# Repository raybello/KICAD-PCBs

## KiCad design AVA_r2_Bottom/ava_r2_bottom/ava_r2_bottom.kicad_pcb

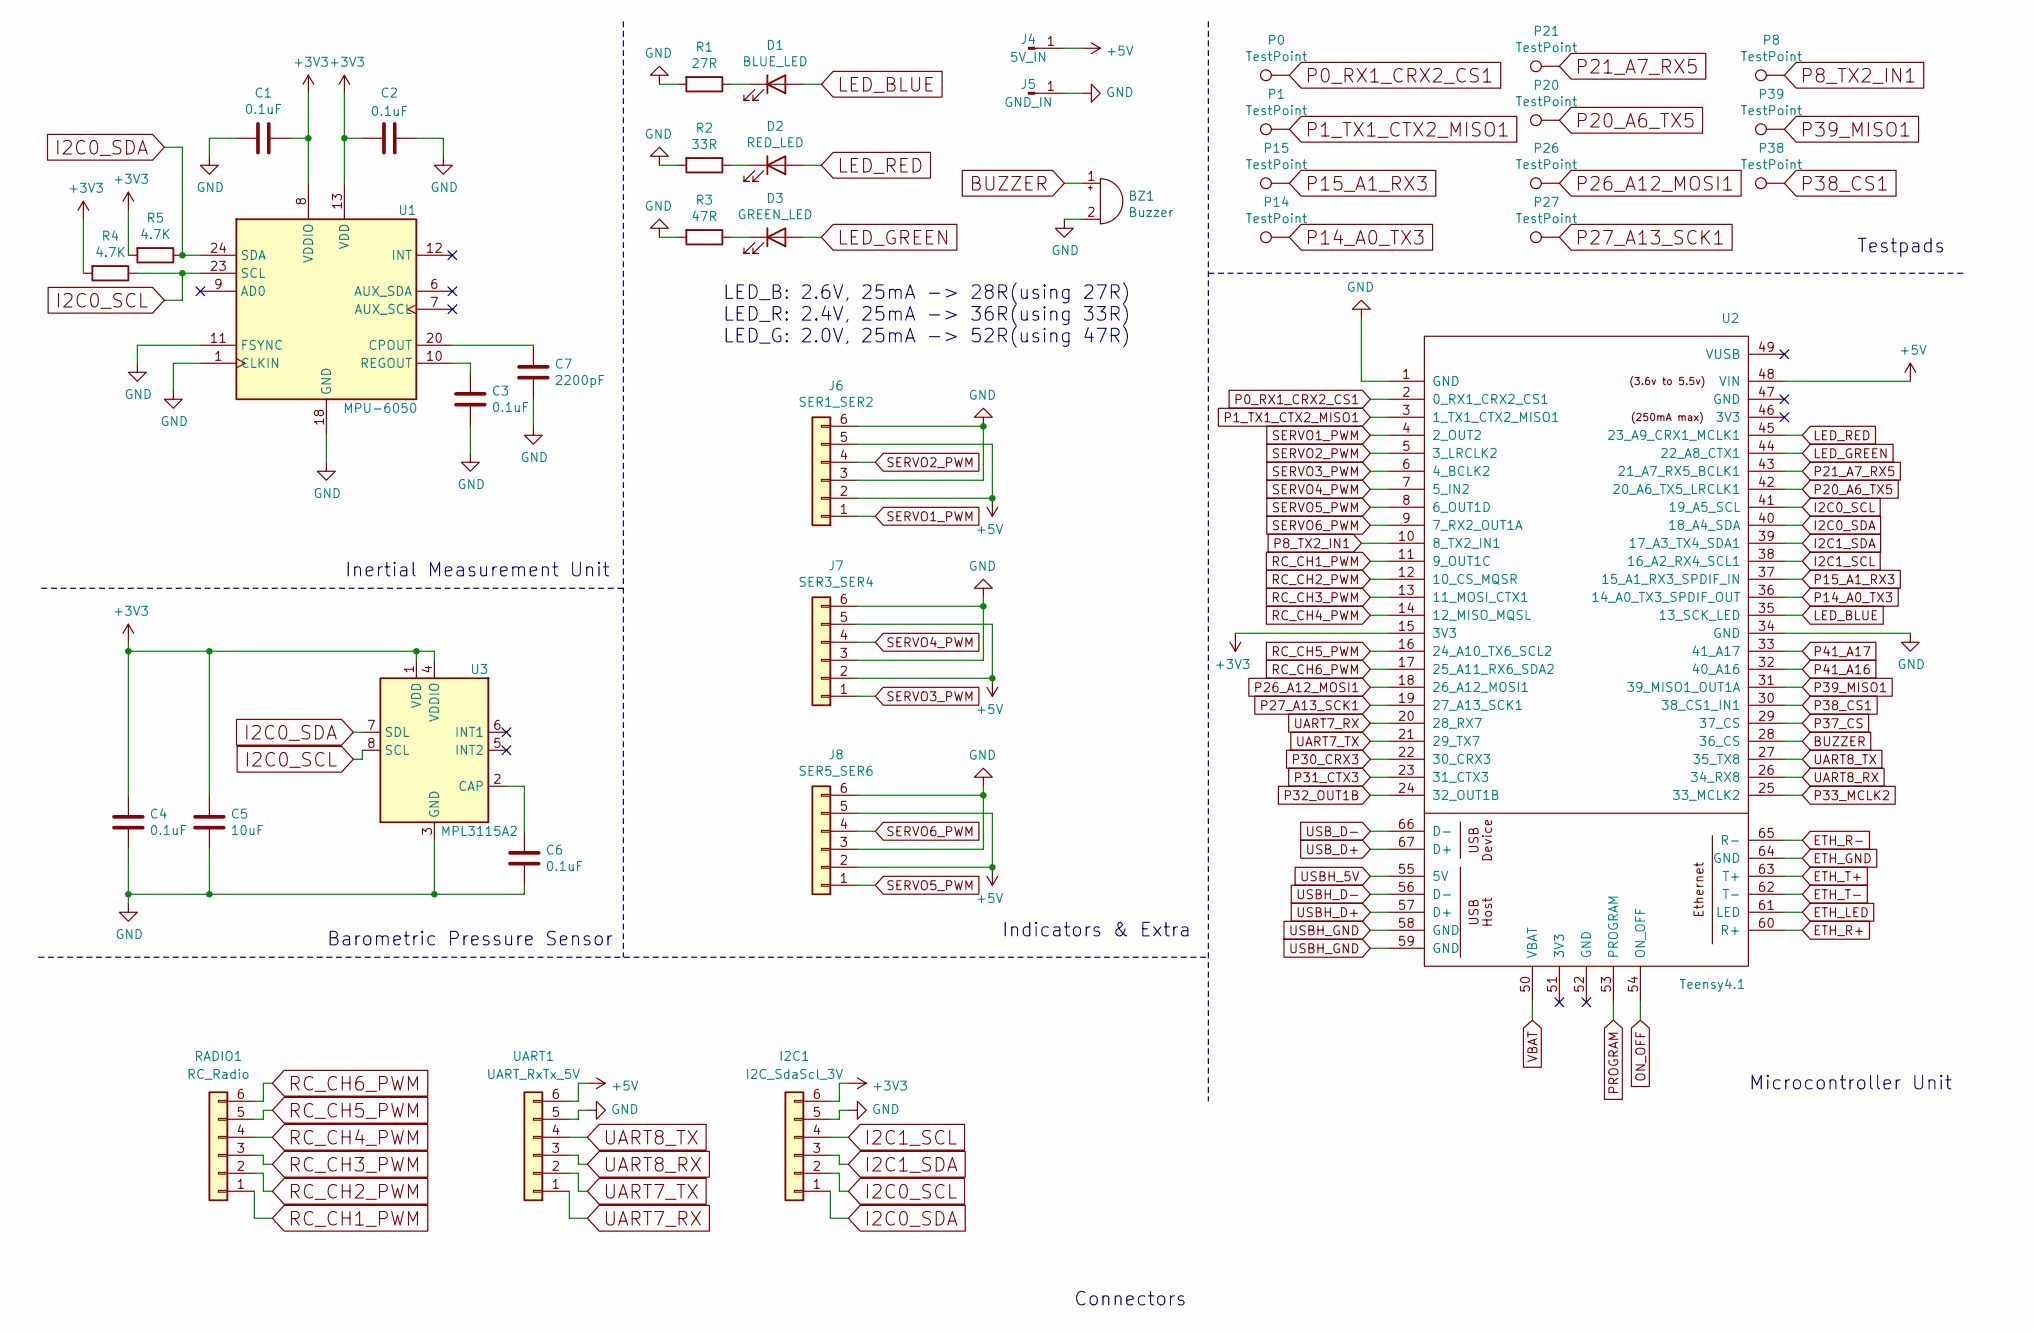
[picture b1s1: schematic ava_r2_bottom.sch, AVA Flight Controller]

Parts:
BZ1: Buzzer; Buzzer_TDK_PS1240P02BT_D12.2mm_H6.5mm
C1, C2, C3, C4, C6: 0.1uF; C_0805_2012Metric_Pad1.18x1.45mm_HandSolder
C5: 10uF; C_0805_2012Metric_Pad1.18x1.45mm_HandSolder
C7: 2200pF; C_0805_2012Metric_Pad1.18x1.45mm_HandSolder
D1: BLUE_LED; LED_0805_2012Metric_Pad1.15x1.40mm_HandSolder
D2: RED_LED; LED_0805_2012Metric_Pad1.15x1.40mm_HandSolder
D3: GREEN_LED; LED_0805_2012Metric_Pad1.15x1.40mm_HandSolder
I2C1: I2C_SdaScl_3V; JST_XH_B6B-XH-A_1x06_P2.50mm_Vertical
J4: 5V_IN; TestPoint_Pad_2.0x2.0mm
J5: GND_IN; TestPoint_Pad_D2.0mm
J6: SER1_SER2; PinHeader_1x06_P1.27mm_Vertical
J7: SER3_SER4; PinHeader_1x06_P1.27mm_Vertical
J8: SER5_SER6; PinHeader_1x06_P1.27mm_Vertical
P0, P1, P8, P14, P15, P20, P21, P26, P27, P38, P39: TestPoint; TestPoint_Pad_2.0x2.0mm
R1: 27R; R_Axial_DIN0207_L6.3mm_D2.5mm_P7.62mm_Horizontal
R2: 33R; R_Axial_DIN0207_L6.3mm_D2.5mm_P7.62mm_Horizontal
R3: 47R; R_Axial_DIN0207_L6.3mm_D2.5mm_P7.62mm_Horizontal
R4, R5: 4.7K; R_Axial_DIN0207_L6.3mm_D2.5mm_P7.62mm_Horizontal
RADIO1: RC_Radio; JST_XH_B6B-XH-A_1x06_P2.50mm_Vertical
U1: MPU-6050; InvenSense_QFN-24_4x4mm_P0.5mm
U2: Teensy4.1; Teensy41
U3: MPL3115A2; NXP_LGA-8_3x5mm_P1.25mm_H1.1mm
UART1: UART_RxTx_5V; JST_XH_B6B-XH-A_1x06_P2.50mm_Vertical

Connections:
+3V3: C1.1, C2.2, C4.2, C5.1, I2C1.6, R4.2, R5.2, U1.8 (VDDIO), U1.13 (VDD), U2.15 (3V3), U3.1 (VDD), U3.4 (VDDIO); also elsewhere on the board
+5V: J4.1, J6.2, J6.5, J7.2, J7.5, J8.2, J8.5, U2.48 (VIN), UART1.6
BUZZER: BZ1.1 (-), U2.28 (36_CS)
ETH_GND: U2.64 (GND)
ETH_LED: U2.61 (LED)
ETH_R+: U2.60 (R+)
ETH_R-: U2.65 (R-)
ETH_T+: U2.63 (T+)
ETH_T-: U2.62 (T-)
GND: BZ1.2 (+), C1.2, C2.1, C3.2, C4.1, C5.2, C6.1, C7.1, I2C1.5, J5.1, J6.3, J6.6, J7.3, J7.6, J8.3, J8.6, R1.2, R2.2, R3.2, U1.1 (CLKIN), U1.11 (FSYNC), U1.18 (GND), U2.1 (GND), U2.34 (GND), U3.3 (GND), UART1.5; also elsewhere on the board
I2C0_SCL: I2C1.2, R4.1, U1.23 (SCL), U2.41 (19_A5_SCL), U3.8 (SCL); also elsewhere on the board
I2C0_SDA: I2C1.1, R5.1, U1.24 (SDA), U2.40 (18_A4_SDA), U3.7 (SDL); also elsewhere on the board
I2C1_SCL: I2C1.4, U2.38 (16_A2_RX4_SCL1)
I2C1_SDA: I2C1.3, U2.39 (17_A3_TX4_SDA1)
LED_BLUE: D1.2 (A), U2.35 (13_SCK_LED)
LED_GREEN: D3.2 (A), U2.44 (22_A8_CTX1)
LED_RED: D2.2 (A), U2.45 (23_A9_CRX1_MCLK1)
unnamed 17: C3.1, U1.10 (REGOUT); also elsewhere on the board
unnamed: C6.2, U3.2 (CAP)
unnamed 19: C7.2, U1.20 (CPOUT); also elsewhere on the board
unnamed: D1.1 (K), R1.1
unnamed: D2.1 (K), R2.1
unnamed: D3.1 (K), R3.1
ON_OFF: U2.54 (ON_OFF)
P0_RX1_CRX2_CS1: P0.1, U2.2 (0_RX1_CRX2_CS1)
P1_TX1_CTX2_MISO1: P1.1, U2.3 (1_TX1_CTX2_MISO1)
P8_TX2_IN1: P8.1, U2.10 (8_TX2_IN1)
P14_A0_TX3: P14.1, U2.36 (14_A0_TX3_SPDIF_OUT)
P15_A1_RX3: P15.1, U2.37 (15_A1_RX3_SPDIF_IN)
P20_A6_TX5: P20.1, U2.42 (20_A6_TX5_LRCLK1)
P21_A7_RX5: P21.1, U2.43 (21_A7_RX5_BCLK1)
P26_A12_MOSI1: P26.1, U2.18 (26_A12_MOSI1)
P27_A13_SCK1: P27.1, U2.19 (27_A13_SCK1)
P30_CRX3: U2.22 (30_CRX3)
P31_CTX3: U2.23 (31_CTX3)
P32_OUT1B: U2.24 (32_OUT1B)
P33_MCLK2: U2.25 (33_MCLK2)
P37_CS: U2.29 (37_CS)
P38_CS1: P38.1, U2.30 (38_CS1_IN1)
P39_MISO1: P39.1, U2.31 (39_MISO1_OUT1A)
P41_A16: U2.32 (40_A16)
P41_A17: U2.33 (41_A17)
PROGRAM: U2.53 (PROGRAM)
RC_CH1_PWM: RADIO1.1, U2.11 (9_OUT1C)
RC_CH2_PWM: RADIO1.2, U2.12 (10_CS_MQSR)
RC_CH3_PWM: RADIO1.3, U2.13 (11_MOSI_CTX1)
RC_CH4_PWM: RADIO1.4, U2.14 (12_MISO_MQSL)
RC_CH5_PWM: RADIO1.5, U2.16 (24_A10_TX6_SCL2)
RC_CH6_PWM: RADIO1.6, U2.17 (25_A11_RX6_SDA2)
SERVO1_PWM: J6.1, U2.4 (2_OUT2)
SERVO2_PWM: J6.4, U2.5 (3_LRCLK2)
SERVO3_PWM: J7.1, U2.6 (4_BCLK2)
SERVO4_PWM: J7.4, U2.7 (5_IN2)
SERVO5_PWM: J8.1, U2.8 (6_OUT1D)
SERVO6_PWM: J8.4, U2.9 (7_RX2_OUT1A)
UART7_RX: U2.20 (28_RX7), UART1.1
UART7_TX: U2.21 (29_TX7), UART1.2
UART8_RX: U2.26 (34_RX8), UART1.3
UART8_TX: U2.27 (35_TX8), UART1.4
USBH_5V: U2.55 (5V)
USBH_D+: U2.57 (D+)
USBH_D-: U2.56 (D-)
USBH_GND: U2.58 (GND), U2.59 (GND)
USB_D+: U2.67 (D+)
USB_D-: U2.66 (D-)
VBAT: U2.50 (VBAT)

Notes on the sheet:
Inertial Measurement Unit
Barometric Pressure Sensor
Connectors
Microcontroller Unit
Indicators & Extra
LED_B: 2.6V, 25mA -> 28R(using 27R) LED_R: 2.4V, 25mA -> 36R(using 33R) LED_G: 2.0V, 25mA -> 52R(using 47R)
Testpads

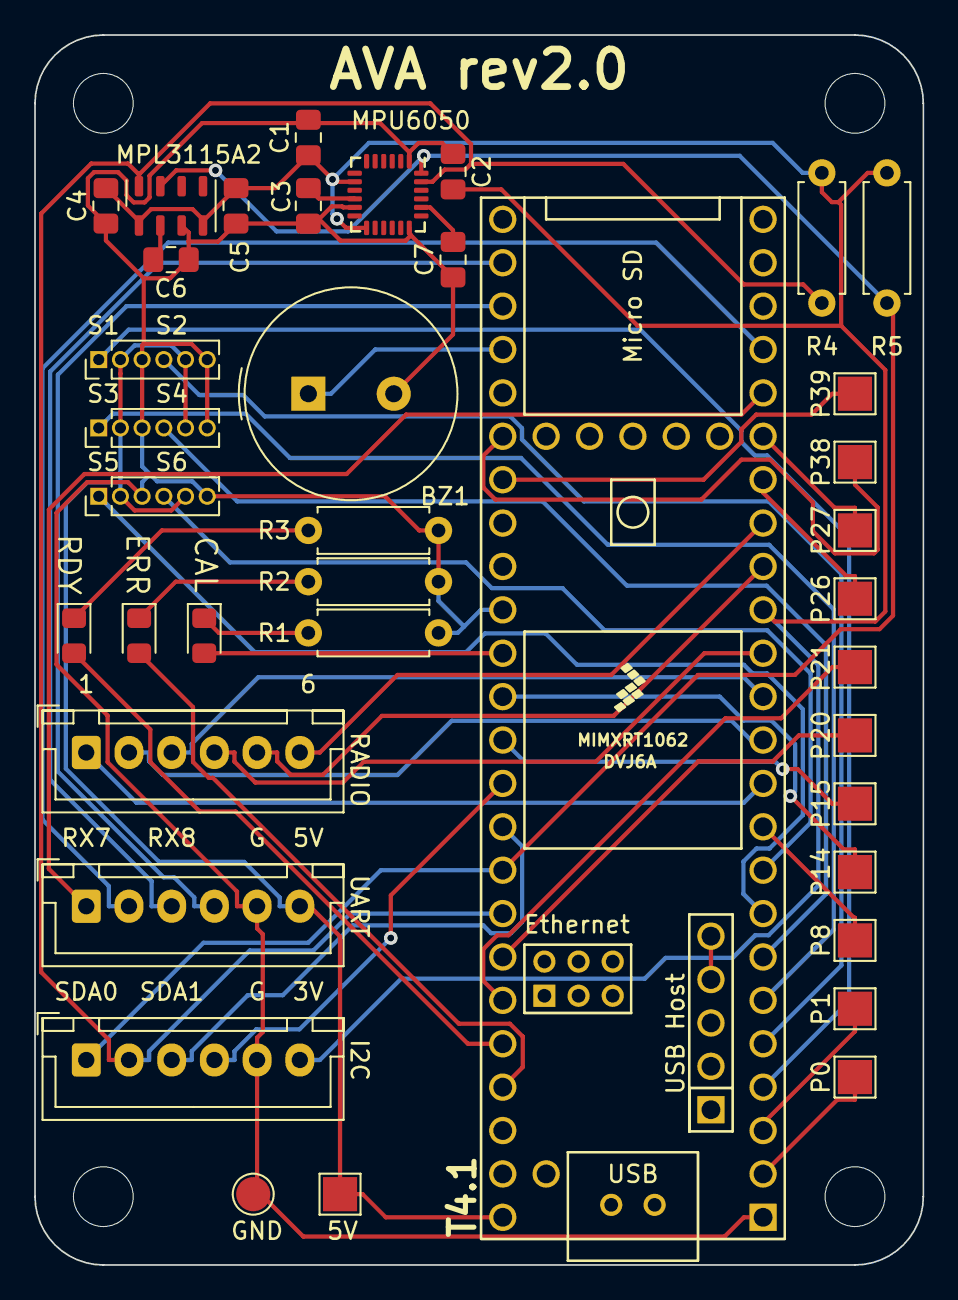
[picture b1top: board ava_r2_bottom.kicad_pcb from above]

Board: 2 copper layers, 52.0 x 72.0 mm, 42 parts (0 on the bottom side), 45 nets.

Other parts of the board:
MPU6050: MPU-6050; InvenSense_QFN-24_4x4mm_P0.5mm
hole1, hole2, hole3, hole4: MountingHole_3.5mm

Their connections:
+3V3: MPU6050.8, MPU6050.13; also elsewhere on the board
GND: MPU6050.1, MPU6050.11, MPU6050.18; also elsewhere on the board
I2C0_SCL: MPU6050.23; also elsewhere on the board
I2C0_SDA: MPU6050.24; also elsewhere on the board
unnamed 17: MPU6050.10; also elsewhere on the board
unnamed 19: MPU6050.20; also elsewhere on the board

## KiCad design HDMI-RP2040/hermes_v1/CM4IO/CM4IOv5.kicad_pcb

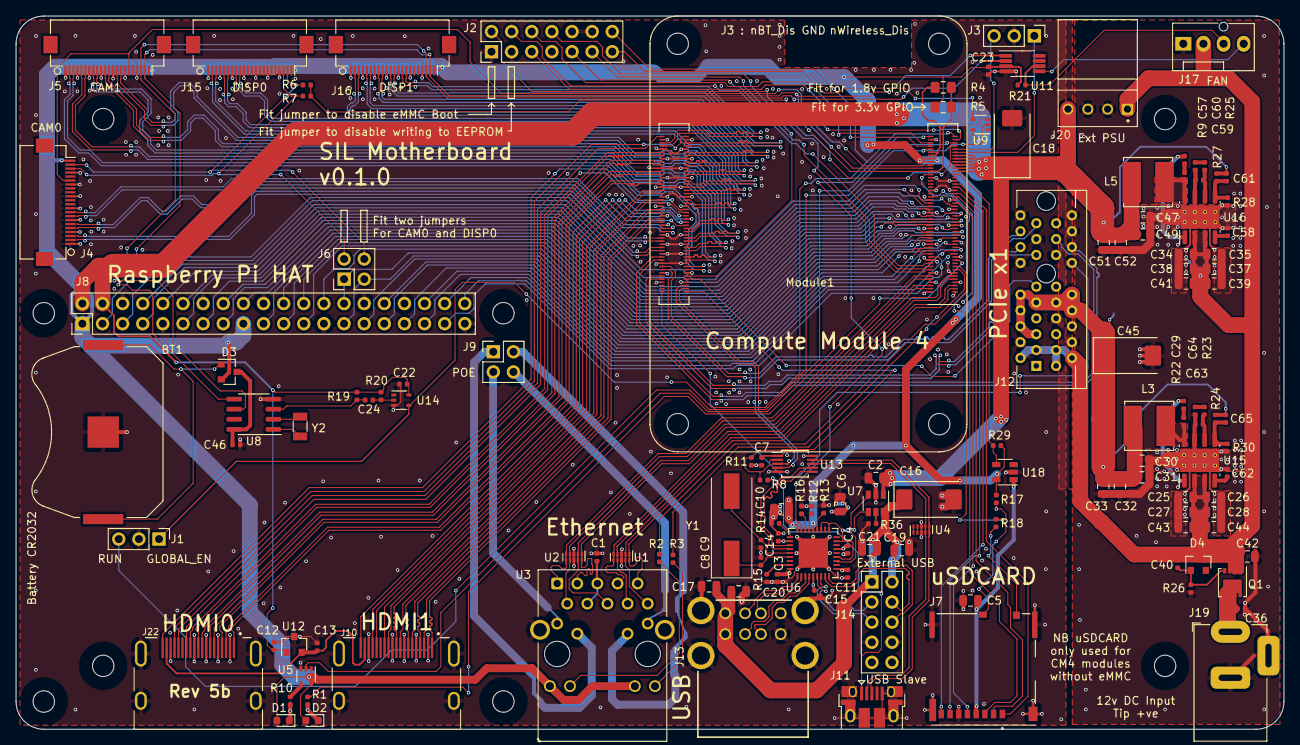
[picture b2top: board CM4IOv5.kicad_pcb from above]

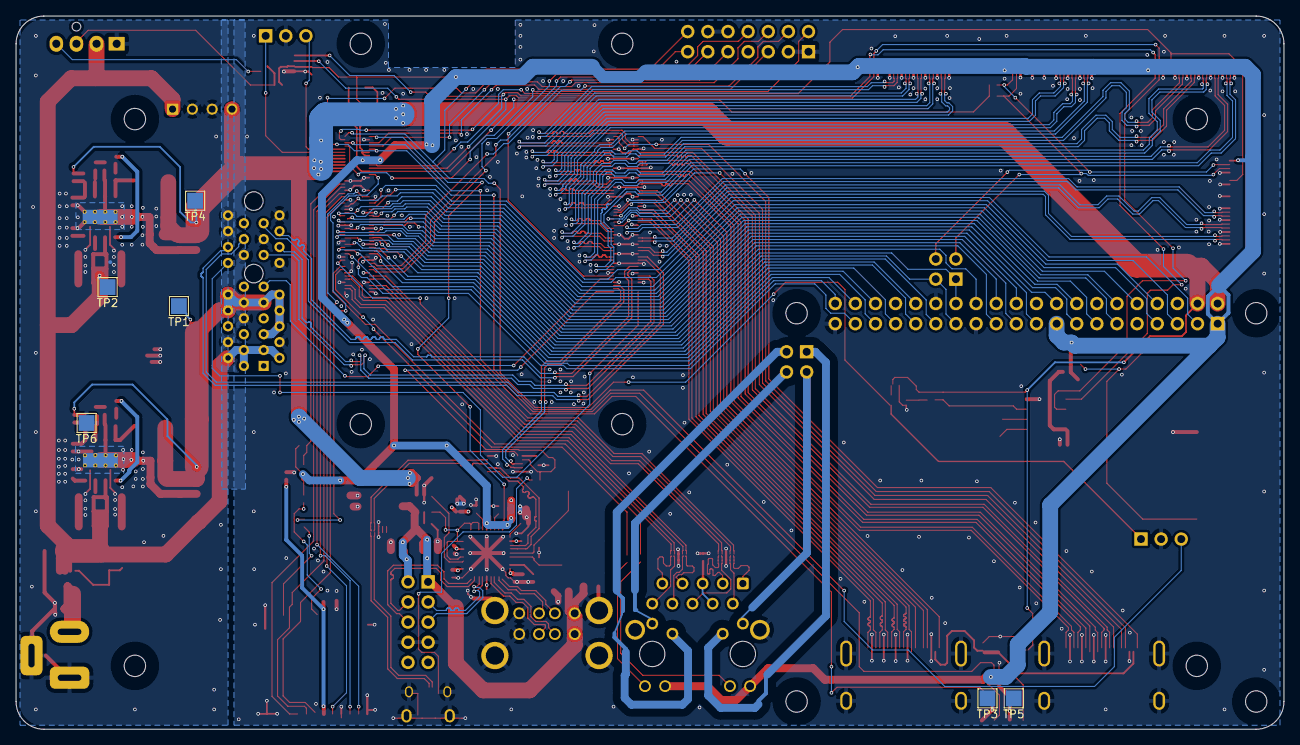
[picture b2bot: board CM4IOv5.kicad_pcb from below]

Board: 4 copper layers, 160.0 x 90.0 mm, 151 parts (6 on the bottom side), 204 nets.

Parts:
BT1: Battery_Cell; BatteryHolder_Keystone_3034_1x20mm
C1, C3, C4, C7, C11, C12, C13, C14, C15, C22, C23, C24, C29, C40, C46, C57, C58, C62: 100n; C_0402_1005Metric
C2, C5, C6, C10, C17, C19, C20, C21, C30, C31, C32, C33, C47, C49, C51, C52: 10u; C_0805_2012Metric
C8, C9: 27pF; C_0402_1005Metric
C16, C18, C45: 100uF; CP_EIA-7343-31_Kemet-D
C25, C26, C27, C28, C34, C35, C37, C38, C39, C41, C42, C43, C44: 10u 35v; C_0805_2012Metric
C36: 100n 100v; C_0402_1005Metric
C59, C61, C63, C65: nf; C_0402_1005Metric
C60, C64: 1.2nF; C_0402_1005Metric
D1: LED Red; LED_0603_1608Metric
D2: LED Green; LED_0603_1608Metric
D3: BAT54C-7-F; SOT-23
D4: MMBZ5242BLT3G; D_SOT-23_ANK
H1, H2, H3, H4, H5, H6, H7, H8: MountingHole; MountingHole_2.7mm_M2.5
J1, J3: Conn_01x03; PinHeader_1x03_P2.54mm_Vertical
J2: Conn_02x07_Odd_Even; PinHeader_2x07_P2.54mm_Vertical
J4, J5, J15, J16: Conn_01x22_Female; Hirose_FH12-22S-0.5SH_1x22-1MP_P0.50mm_Horizontal
J6, J9: THD-02-R; PinHeader_2x02_P2.54mm_Vertical
J7: Micro_SD_Card_Det; SDCARD_MOLEX_503398-1892
J8: THD-20-R; PinHeader_2x20_P2.54mm_Vertical
J10, J22: 690-019-298-412; EDAC 690-019-298-412
J11: USB_OTG; USB_Micro-B_EDAC_UCON00686
J12: 10018783-11200TLF; PCIex1-36
J13: 690-008-221-904; MOLEX_USB_67298-4090
J14: Conn_02x05_Odd_Even; PinHeader_2x05_P2.54mm_Vertical
J17: Molex 470531000; FanPinHeader_1x04_P2.54mm_Vertical
J19: Barrel_Jack; BarrelJack_Horizontal
J20: AMP171826-4; TE_171826-4
L3, L5: SRN6045TA-3R3Y; L_Bourns_SRN6045TA
Module1: ComputeModule4; Raspberry-Pi-4-Compute-Module
Q1: DMP3013SFV-7; Diodes_PowerDI3333-8
R1, R10: 1k; R_0402_1005Metric
R2, R3: 470R; R_0402_1005Metric
R4: nf; R_0805_2012Metric_Pad1.15x1.40mm_HandSolder
R5: 0R; R_0805_2012Metric_Pad1.15x1.40mm_HandSolder
R6, R7, R8, R11, R28: 2.2K 1%; R_0402_1005Metric
R9, R22: 10R; R_0402_1005Metric
R12, R13, R14, R16, R21: 36K 1%; R_0402_1005Metric
R15, R23, R26, R27, R29: 12K 1%; R_0402_1005Metric
R17, R18: nf; R_0402_1005Metric
R19, R20: 510K 1%; R_0402_1005Metric
R24: 47K 1%; R_0402_1005Metric
R25: 20K 1%; R_0402_1005Metric
R30, R36: 15K 1%; R_0402_1005Metric
TP1, TP2, TP3, TP4, TP5, TP6: TestPoint; TestPoint_Pad_2.0x2.0mm
U1, U2, U4: TPD4EUSB30; USON-10_2.5x1.0mm_P0.5mm
U3: MagJack-A70-112-331N126; TRJG0926HENL
U5, U9, U14: 74LVC1G07SE-7; SOT-353_SC-70-5
U6: USB2514B-I/M2; QFN-36-1EP_6x6mm_P0.5mm_EP3.7x3.7mm
U7: AP22653W6; SOT-23-6
U8: PCF85063AT/AAZ; SOIC-8_3.9x4.9mm_P1.27mm
U11: EMC2301-1-ACZL-TR; MSOP-8_3x3mm_P0.65mm
U12: RT9742SNGV; SOT-23
U13: FSUSB42MUX; MSOP-10_3x3mm_P0.5mm
U15, U16: AP64501SP-13; SOIC-8-1EP_3.9x4.9mm_P1.27mm_EP2.95x4.9mm_Mask2.71x3.4mm_Th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
U18: RT9742GGJ5; SOT-23-5
Y1: 24MHz; Crystal_SMD_HC49-SD
Y2: X32K768S301; Crystal_SMD_3215-2Pin_3.2x1.5mm

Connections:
/+3.3v: C3.1, C4.1, C6.1, C7.1, C10.1, C11.1, C14.1, C15.1, C23.1, D1.2 (A), D2.2 (A), D3.2, J4.22, J5.22, J8.1, J8.17, J15.22, J16.22, Module1.84 (+3.3v_(Output)), Module1.86 (+3.3v_(Output)), R5.1, R17.1, R21.2, R29.1, U3.15 (LEDG_A), U3.17 (LEDY_A), U5.5 (VCC), U6.5 (VDDA33), U6.10 (VDDA33), U6.15 (VDD33), U6.23 (VDD33), U6.27 (VBUS_DET), U6.29 (VDDA33), U6.36 (VDDA33), U11.3 (VDD), U13.1 (VCC), U18.5 (IN)
/+5v: C2.1, C12.1, C18.1, C22.1, C47.1, C49.1, C51.1, C52.1, C61.1, J8.2, J8.4, J20.4, L5.2, Module1.77 (+5v_(Input)), Module1.79 (+5v_(Input)), Module1.81 (+5v_(Input)), Module1.83 (+5v_(Input)), Module1.85 (+5v_(Input)), Module1.87 (+5v_(Input)), R19.2, R20.2, R27.1, TP4.1, U7.1 (IN), U9.5 (VCC), U12.1 (IN), U14.5 (VCC)
/+12v: C25.1, C26.1, C27.1, C28.1, C34.1, C35.1, C37.1, C38.1, C39.1, C40.1, C41.1, C42.1, C43.1, C44.1, D4.1 (K), J12.A2 (+12V), J12.A3 (+12V), J12.B1 (+12v), J12.B2 (+12v), J12.B3 (+12v), J17.2, J20.1, Q1.1 (S), Q1.2 (S), Q1.3 (S), TP2.1, U15.2 (VIN), U15.3 (EN), U16.2 (VIN), U16.3 (EN)
/CAM_GPIO: J4.17, J5.17, Module1.97 (Camera_GPIO)
/CM4_GPIO ( Ethernet, GPIO, SDCARD)/+1.8v: Module1.88 (+1.8v_(Output)), Module1.90 (+1.8v_(Output)), R4.1
/CM4_GPIO ( Ethernet, GPIO, SDCARD)/AIN0: J2.5, Module1.96 (AnalogIP0)
/CM4_GPIO ( Ethernet, GPIO, SDCARD)/AIN1: J2.6, Module1.94 (AnalogIP1)
/CM4_GPIO ( Ethernet, GPIO, SDCARD)/BT_nDis: J3.3, Module1.91 (BT_nDisable)
/CM4_GPIO ( Ethernet, GPIO, SDCARD)/EEPROM_nWP: J2.4, Module1.20 (EEPROM_nWP)
/CM4_GPIO ( Ethernet, GPIO, SDCARD)/ETH_LEDG: Module1.17 (Ethernet_nLED2(3.3v)), R2.2
/CM4_GPIO ( Ethernet, GPIO, SDCARD)/ETH_LEDY: Module1.15 (Ethernet_nLED3(3.3v)), R3.2
/CM4_GPIO ( Ethernet, GPIO, SDCARD)/GPIO2: J8.3, Module1.58 (GPIO2)
/CM4_GPIO ( Ethernet, GPIO, SDCARD)/GPIO3: J8.5, Module1.56 (GPIO3)
/CM4_GPIO ( Ethernet, GPIO, SDCARD)/GPIO4: J8.7, Module1.54 (GPIO4)
/CM4_GPIO ( Ethernet, GPIO, SDCARD)/GPIO5: J8.29, Module1.34 (GPIO5)
/CM4_GPIO ( Ethernet, GPIO, SDCARD)/GPIO6: J8.31, Module1.30 (GPIO6)
/CM4_GPIO ( Ethernet, GPIO, SDCARD)/GPIO7: J8.26, Module1.37 (GPIO7)
/CM4_GPIO ( Ethernet, GPIO, SDCARD)/GPIO8: J8.24, Module1.39 (GPIO8)
/CM4_GPIO ( Ethernet, GPIO, SDCARD)/GPIO9: J8.21, Module1.40 (GPIO9)
/CM4_GPIO ( Ethernet, GPIO, SDCARD)/GPIO10: J8.19, Module1.44 (GPIO10)
/CM4_GPIO ( Ethernet, GPIO, SDCARD)/GPIO11: J8.23, Module1.38 (GPIO11)
/CM4_GPIO ( Ethernet, GPIO, SDCARD)/GPIO12: J8.32, Module1.31 (GPIO12)
/CM4_GPIO ( Ethernet, GPIO, SDCARD)/GPIO13: J8.33, Module1.28 (GPIO13)
/CM4_GPIO ( Ethernet, GPIO, SDCARD)/GPIO14: J8.8, Module1.55 (GPIO14)
/CM4_GPIO ( Ethernet, GPIO, SDCARD)/GPIO15: J8.10, Module1.51 (GPIO15)
/CM4_GPIO ( Ethernet, GPIO, SDCARD)/GPIO16: J8.36, Module1.29 (GPIO16)
/CM4_GPIO ( Ethernet, GPIO, SDCARD)/GPIO17: J8.11, Module1.50 (GPIO17)
/CM4_GPIO ( Ethernet, GPIO, SDCARD)/GPIO18: J8.12, Module1.49 (GPIO18)
/CM4_GPIO ( Ethernet, GPIO, SDCARD)/GPIO19: J8.35, Module1.26 (GPIO19)
/CM4_GPIO ( Ethernet, GPIO, SDCARD)/GPIO20: J8.38, Module1.27 (GPIO20)
/CM4_GPIO ( Ethernet, GPIO, SDCARD)/GPIO21: J8.40, Module1.25 (GPIO21)
/CM4_GPIO ( Ethernet, GPIO, SDCARD)/GPIO22: J8.15, Module1.46 (GPIO22)
/CM4_GPIO ( Ethernet, GPIO, SDCARD)/GPIO23: J8.16, Module1.47 (GPIO23)
/CM4_GPIO ( Ethernet, GPIO, SDCARD)/GPIO24: J8.18, Module1.45 (GPIO24)
/CM4_GPIO ( Ethernet, GPIO, SDCARD)/GPIO25: J8.22, Module1.41 (GPIO25)
/CM4_GPIO ( Ethernet, GPIO, SDCARD)/GPIO26: J8.37, Module1.24 (GPIO26)
/CM4_GPIO ( Ethernet, GPIO, SDCARD)/GPIO27: J8.13, Module1.48 (GPIO27)
/CM4_GPIO ( Ethernet, GPIO, SDCARD)/RUN_PG: J1.3, Module1.92 (RUN_PG), U9.2
/CM4_GPIO ( Ethernet, GPIO, SDCARD)/Reserved: Module1.76 (Reserved), R18.1
/CM4_GPIO ( Ethernet, GPIO, SDCARD)/SD_CLK: J7.5 (CLK), Module1.57 (SD_CLK)
/CM4_GPIO ( Ethernet, GPIO, SDCARD)/SD_CMD: J7.3 (CMD), Module1.62 (SD_CMD)
/CM4_GPIO ( Ethernet, GPIO, SDCARD)/SD_DAT0: J7.7 (DAT0), Module1.63 (SD_DAT0)
/CM4_GPIO ( Ethernet, GPIO, SDCARD)/SD_DAT1: J7.8 (DAT1), Module1.67 (SD_DAT1)
/CM4_GPIO ( Ethernet, GPIO, SDCARD)/SD_DAT2: J7.1 (DAT2), Module1.69 (SD_DAT2)
/CM4_GPIO ( Ethernet, GPIO, SDCARD)/SD_DAT3: J7.2 (DAT3/CD), Module1.61 (SD_DAT3)
/CM4_GPIO ( Ethernet, GPIO, SDCARD)/SD_PWR: C5.1, J7.4 (VDD), U18.1 (OUT)
/CM4_GPIO ( Ethernet, GPIO, SDCARD)/SD_PWR_ON: Module1.75 (SD_PWR_ON), R29.2, U18.4 (EN)
/CM4_GPIO ( Ethernet, GPIO, SDCARD)/SYNC_IN: J2.8, Module1.16 (Ethernet_SYNC_IN(1.8v))
/CM4_GPIO ( Ethernet, GPIO, SDCARD)/SYNC_OUT: J2.9, Module1.18 (Ethernet_SYNC_OUT(1.8v))
/CM4_GPIO ( Ethernet, GPIO, SDCARD)/TR0_TAP: J9.3, U3.11 (VC1)
/CM4_GPIO ( Ethernet, GPIO, SDCARD)/TR1_TAP: J9.1, U3.12 (VC2)
/CM4_GPIO ( Ethernet, GPIO, SDCARD)/TR2_TAP: J9.2, U3.13 (VC3)
/CM4_GPIO ( Ethernet, GPIO, SDCARD)/TR3_TAP: J9.4, U3.14 (VC4)
/CM4_GPIO ( Ethernet, GPIO, SDCARD)/TRD0_N: Module1.10 (Ethernet_Pair0_N), U2.4 (D2+), U2.7, U3.2 (TRD0-)
/CM4_GPIO ( Ethernet, GPIO, SDCARD)/TRD0_P: Module1.12 (Ethernet_Pair0_P), U2.5 (D2-), U2.6, U3.1 (TRD0+)
/CM4_GPIO ( Ethernet, GPIO, SDCARD)/TRD1_N: Module1.6 (Ethernet_Pair1_N), U2.2 (D1-), U2.9, U3.6 (TRD1-)
/CM4_GPIO ( Ethernet, GPIO, SDCARD)/TRD1_P: Module1.4 (Ethernet_Pair1_P), U2.1 (D1+), U2.10, U3.3 (TRD1+)
/CM4_GPIO ( Ethernet, GPIO, SDCARD)/TRD2_N: Module1.9 (Ethernet_Pair2_N), U1.4 (D2+), U1.7, U3.8 (TRD2-)
/CM4_GPIO ( Ethernet, GPIO, SDCARD)/TRD2_P: Module1.11 (Ethernet_Pair2_P), U1.5 (D2-), U1.6, U3.7 (TRD2+)
/CM4_GPIO ( Ethernet, GPIO, SDCARD)/TRD3_N: Module1.5 (Ethernet_Pair3_N), U1.2 (D1-), U1.9, U3.10 (TRD3-)
/CM4_GPIO ( Ethernet, GPIO, SDCARD)/TRD3_P: Module1.3 (Ethernet_Pair3_P), U1.1 (D1+), U1.10, U3.9 (TRD3+)
/CM4_GPIO ( Ethernet, GPIO, SDCARD)/WL_nDis: J3.1, Module1.89 (WL_nDisable)
/CM4_GPIO ( Ethernet, GPIO, SDCARD)/nPWR_LED: Module1.95 (nPI_LED_PWR), U5.2
/CM4_GPIO ( Ethernet, GPIO, SDCARD)/nRPIBOOT: J2.2, Module1.93 (nRPIBOOT)
/CM4_HighSpeed/CAM0_C_N: J4.8, Module1.140 (CAM0_C_N)
/CM4_HighSpeed/CAM0_C_P: J4.9, Module1.142 (CAM0_C_P)
/CM4_HighSpeed/CAM0_D0_N: J4.2, Module1.128 (CAM0_D0_N)
/CM4_HighSpeed/CAM0_D0_P: J4.3, Module1.130 (CAM0_D0_P)
/CM4_HighSpeed/CAM0_D1_N: J4.5, Module1.134 (CAM0_D1_N)
/CM4_HighSpeed/CAM0_D1_P: J4.6, Module1.136 (CAM0_D1_P)
/CM4_HighSpeed/CAM1_C_N: J5.8, Module1.127 (CAM1_C_N)
/CM4_HighSpeed/CAM1_C_P: J5.9, Module1.129 (CAM1_C_P)
/CM4_HighSpeed/CAM1_D0_N: J5.2, Module1.115 (CAM1_D0_N)
/CM4_HighSpeed/CAM1_D0_P: J5.3, Module1.117 (CAM1_D0_P)
/CM4_HighSpeed/CAM1_D1_N: J5.5, Module1.121 (CAM1_D1_N)
/CM4_HighSpeed/CAM1_D1_P: J5.6, Module1.123 (CAM1_D1_P)
/CM4_HighSpeed/CAM1_D2_N: J5.11, Module1.133 (CAM1_D2_N)
/CM4_HighSpeed/CAM1_D2_P: J5.12, Module1.135 (CAM1_D2_P)
/CM4_HighSpeed/CAM1_D3_N: J5.14, Module1.139 (CAM1_D3_N)
/CM4_HighSpeed/CAM1_D3_P: J5.15, Module1.141 (CAM1_D3_P)
/CM4_HighSpeed/DSI0_C_N: J15.8, Module1.169 (DSI0_C_N)
/CM4_HighSpeed/DSI0_C_P: J15.9, Module1.171 (DSI0_C_P)
/CM4_HighSpeed/DSI0_D0_N: J15.2, Module1.157 (DSI0_D0_N)
/CM4_HighSpeed/DSI0_D0_P: J15.3, Module1.159 (DSI0_D0_P)
/CM4_HighSpeed/DSI0_D1_N: J15.5, Module1.163 (DSI0_D1_N)
/CM4_HighSpeed/DSI0_D1_P: J15.6, Module1.165 (DSI0_D1_P)
/CM4_HighSpeed/DSI1_C_N: J16.8, Module1.187 (DSI1_C_N)
/CM4_HighSpeed/DSI1_C_P: J16.9, Module1.189 (DSI1_C_P)
/CM4_HighSpeed/DSI1_D0_N: J16.2, Module1.175 (DSI1_D0_N)
/CM4_HighSpeed/DSI1_D0_P: J16.3, Module1.177 (DSI1_D0_P)
/CM4_HighSpeed/DSI1_D1_N: J16.5, Module1.181 (DSI1_D1_N)
/CM4_HighSpeed/DSI1_D1_P: J16.6, Module1.183 (DSI1_D1_P)
/CM4_HighSpeed/DSI1_D2_N: J16.11, Module1.193 (DSI1_D2_N)
/CM4_HighSpeed/DSI1_D2_P: J16.12, Module1.195 (DSI1_D2_P)
/CM4_HighSpeed/DSI1_D3_N: J16.14, Module1.194 (DSI1_D3_N)
/CM4_HighSpeed/DSI1_D3_P: J16.15, Module1.196 (DSI1_D3_P)
/CM4_HighSpeed/HDMI0_CEC: J22.13 (CEC), Module1.151 (HDMI0_CEC)
/CM4_HighSpeed/HDMI0_CK_N: J22.12 (CK-), Module1.190 (HDMI0_CLK_N)
/CM4_HighSpeed/HDMI0_CK_P: J22.10 (CK+), Module1.188 (HDMI0_CLK_P)
/CM4_HighSpeed/HDMI0_D0_N: J22.9 (D0-), Module1.184 (HDMI0_TX0_N)
/CM4_HighSpeed/HDMI0_D0_P: J22.7 (D0+), Module1.182 (HDMI0_TX0_P)
/CM4_HighSpeed/HDMI0_D1_N: J22.6 (D1-), Module1.178 (HDMI0_TX1_N)
/CM4_HighSpeed/HDMI0_D1_P: J22.4 (D1+), Module1.176 (HDMI0_TX1_P)
/CM4_HighSpeed/HDMI0_D2_N: J22.3 (D2-), Module1.172 (HDMI0_TX2_N)
/CM4_HighSpeed/HDMI0_D2_P: J22.1 (D2+), Module1.170 (HDMI0_TX2_P)
/CM4_HighSpeed/HDMI0_HOTPLUG: J22.19 (HPD/HEAC-), Module1.153 (HDMI0_HOTPLUG)
/CM4_HighSpeed/HDMI0_SCL: J22.15 (SCL), Module1.200 (HDMI0_SCL)
/CM4_HighSpeed/HDMI0_SDA: J22.16 (SDA), Module1.199 (HDMI0_SDA)
/CM4_HighSpeed/HDMI1_CEC: J10.13 (CEC), Module1.149 (HDMI1_CEC)
/CM4_HighSpeed/HDMI1_CK_N: J10.12 (CK-), Module1.166 (HDMI1_CLK_N)
/CM4_HighSpeed/HDMI1_CK_P: J10.10 (CK+), Module1.164 (HDMI1_CLK_P)
/CM4_HighSpeed/HDMI1_D0_N: J10.9 (D0-), Module1.160 (HDMI1_TX0_N)
/CM4_HighSpeed/HDMI1_D0_P: J10.7 (D0+), Module1.158 (HDMI1_TX0_P)
/CM4_HighSpeed/HDMI1_D1_N: J10.6 (D1-), Module1.154 (HDMI1_TX1_N)
/CM4_HighSpeed/HDMI1_D1_P: J10.4 (D1+), Module1.152 (HDMI1_TX1_P)
/CM4_HighSpeed/HDMI1_D2_N: J10.3 (D2-), Module1.148 (HDMI1_TX2_N)
/CM4_HighSpeed/HDMI1_D2_P: J10.1 (D2+), Module1.146 (HDMI1_TX2_P)
/CM4_HighSpeed/HDMI1_HOTPLUG: J10.19 (HPD/HEAC-), Module1.143 (HDMI1_HOTPLUG)
/CM4_HighSpeed/HDMI1_SCL: J10.15 (SCL), Module1.147 (HDMI1_SCL)
/CM4_HighSpeed/HDMI1_SDA: J10.16 (SDA), Module1.145 (HDMI1_SDA)
/CM4_HighSpeed/HDMI_5v: C13.1, J10.18 (+5V), J22.18 (+5V), U12.2 (OUT)
/CM4_HighSpeed/SCL1: J4.20, J6.2, J15.20, R7.2
/CM4_HighSpeed/SDA1: J4.21, J6.4, J15.21, R6.2
/GLOBAL_EN: J1.1, J2.14, Module1.99 (Global_EN), U14.4
/GPIO_VREF: Module1.78 (GPIO_VREF(1.8v/3.3v_Input)), R4.2, R5.2, R6.1, R7.1
/ID_SC: J6.1, J8.28, Module1.35 (ID_SC)
/ID_SD: J6.3, J8.27, Module1.36 (ID_SD)
/PCIE_CLK_N: J12.A14 (REFCLK-), Module1.112 (PCIe_CLK_N)
/PCIE_CLK_P: J12.A13 (REFCLK+), Module1.110 (PCIe_CLK_P)
/PCIE_CLK_nREQ: J12.B12 (nCLKREQ), Module1.102 (PCIe_CLK_nREQ)
/PCIE_RX_N: J12.A16 (PERP0), Module1.118 (PCIe_RX_N)
/PCIE_RX_P: J12.A17 (PERN0), Module1.116 (PCIe_RX_P)
/PCIE_TX_N: J12.B14 (PETP0), Module1.124 (PCIe_TX_N)
/PCIE_TX_P: J12.B15 (PETN0), Module1.122 (PCIe_TX_P)
/PCIE_nRST: J12.A11 (nPERST), Module1.109 (PCIe_nRST)
/PCIe-connector/+3.3v: C30.1, C31.1, C32.1, C33.1, C45.1, C65.1, J12.A5 (TCK), J12.A6 (TDI), J12.A8 (TMS), J12.A9 (+3.3V), J12.A10 (+3.3V), J12.B8 (+3.3v), J12.B9 (nTRST), J12.B10 (+3.3vAUX), L3.2, R24.1, TP1.1
/RTC , Wakeup, FAN/nRTC_INT: C24.2, R19.1, U8.3 (~INT~)
/SCL0: J5.20, J16.20, Module1.80 (SCL0), U8.6 (SCL), U11.2 (SCL)
/SDA0: J5.21, J16.21, Module1.82 (SDA0), U8.5 (SDA), U11.1 (SDA)
/TV_OUT: J2.11, Module1.111 (VDAC_COMP)
/USB2-HUB/HD1_N: J13.2 (D-`), U6.1 (USBDM_DN1/PRT_DIS_M1)
/USB2-HUB/HD1_P: J13.3 (D+`), U6.2 (USBDP_DN1/PRT_DIS_P1)
/USB2-HUB/HD2_N: J13.6 (D-), U6.3 (USBDM_DN2/PRT_DIS_M2)
/USB2-HUB/HD2_P: J13.7 (D+), U6.4 (USBDP_DN2/PRT_DIS_P2)
/USB2-HUB/HD3_N: J14.3, U6.6 (USBDM_DN3/PRT_DIS_M3)
/USB2-HUB/HD3_P: J14.5, U6.7 (USBDP_DN3/PRT_DIS_P3)
/USB2-HUB/HD4_N: J14.4, U6.8 (USBDM_DN4/PRT_DIS_M4)
/USB2-HUB/HD4_P: J14.6, U6.9 (USBDP_DN4/PRT_DIS_P4)
/USB2-HUB/PWR1: U6.12 (PRTPWR1/BC_EN1), U7.3 (EN)
/USB2-HUB/USBD_N: J11.2 (D-), U4.4 (D2+), U4.7, U13.8 (HSD1_M)
/USB2-HUB/USBD_P: J11.3 (D+), U4.5 (D2-), U4.6, U13.9 (HSD1_P)
/USB2-HUB/USBH_N: U6.30 (USBDM_UP), U13.6 (HSD0_M)
/USB2-HUB/USBH_P: U6.31 (USBDP_UP), U13.7 (HSD0_P)
/USB2-HUB/VBUS: C16.1, C17.1, C19.1, C20.1, C21.1, J13.1 (VBUS`), J13.5 (VBUS), J14.1, J14.2, U7.6 (OUT)
/USB2-HUB/nOCS1: U6.13 (OCS_N1), U6.17 (OCS_N2), U6.19 (OCS_N3), U6.21 (OCS_N4), U7.4 (nFault)
/USB2_N: Module1.103 (USB2_N), U13.4 (D_N)
/USB2_P: Module1.105 (USB2_P), U13.3 (D_P)
/USBOTG: Module1.101 (USB_OTG_ID), R8.2, R11.1, U13.2 (SEL)
/nEXTRST: Module1.100 (nEXTRST), U6.26 (RESET_N)
GND: BT1.2 (-), C1.2, C2.2, C3.2, C4.2, C5.2, C6.2, C7.2, C8.2, C9.2, C10.2, C11.2, C12.2, C13.2, C14.2, C15.2, C16.2, C17.2, C18.2, C19.2, C20.2, C21.2, C22.2, C23.2, C25.2, C26.2, C27.2, C28.2, C30.2, C31.2, C32.2, C33.2, C34.2, C35.2, C36.2, C37.2, C38.2, C39.2, C41.2, C42.2, C43.2, C44.2, C45.2, C46.2, C47.2, C49.2, C51.2, C52.2, C58.2, C59.2, C60.2, C62.2, C63.2, C64.2, J1.2, J2.1, J2.3, J2.7, J2.10, J2.12, J3.2, J4.1, J4.4, J4.7, J4.10, J4.13, J4.16, J4.19, J5.1, J5.4, J5.7, J5.10, J5.13, J5.16, J5.19, J7.6 (VSS), J7.11 (SHIELD), J8.6, J8.9, J8.14, J8.20, J8.25, J8.30, J8.34, J8.39, J10.2 (D2S), J10.5 (D1S), J10.8 (D0S), J10.11 (CKS), J10.17 (GND), J10.SH1 (SH), J10.SH2 (SH), J10.SH3 (SH), J10.SH4 (SH), J11.5 (GND), J11.6 (Shield), J12.A4 (GND), J12.A12 (GND), J12.A15 (GND), J12.A18 (GND), J12.B4 (GND), J12.B7 (GND), J12.B13 (GND), J12.B16 (GND), J12.B18 (GND), J13.4 (GND`), J13.8 (GND), J13.MT1, J13.MT2, J13.MT3, J13.MT4, J14.7, J14.8, J15.1, J15.4, J15.7, J15.10, J15.13, J15.16, J15.19, J16.1, J16.4, J16.7, J16.10, J16.13, J16.16, J16.19, J17.1, J19.2, J19.3, J20.2, J20.3, J22.2 (D2S), J22.5 (D1S), J22.8 (D0S), J22.11 (CKS), J22.17 (GND), J22.SH1 (SH), J22.SH2 (SH), J22.SH3 (SH), J22.SH4 (SH), Module1.1 (GND), Module1.2 (GND), Module1.7 (GND), Module1.8 (GND), Module1.13 (GND), Module1.14 (GND), Module1.22 (GND), Module1.23 (GND), Module1.32 (GND), Module1.33 (GND), Module1.42 (GND), Module1.43 (GND), Module1.52 (GND), Module1.53 (GND), Module1.59 (GND), Module1.60 (GND), Module1.65 (GND), Module1.66 (GND), Module1.71 (GND), Module1.74 (GND), Module1.98 (GND), Module1.107 (GND), Module1.108 (GND), Module1.113 (GND), Module1.114 (GND), Module1.119 (GND), Module1.120 (GND), Module1.125 (GND), Module1.126 (GND), Module1.131 (GND), Module1.132 (GND), Module1.137 (GND), Module1.138 (GND), Module1.144 (GND), Module1.150 (GND), Module1.155 (GND), Module1.156 (GND), Module1.161 (GND), Module1.162 (GND), Module1.167 (GND), Module1.168 (GND), Module1.173 (GND), Module1.174 (GND), Module1.179 (GND), Module1.180 (GND), Module1.185 (GND), Module1.186 (GND), Module1.191 (GND), Module1.192 (GND), Module1.197 (GND), Module1.198 (GND), R11.2, R12.2, R13.2, R14.2, R15.1, R16.2, R26.2, R28.2, R30.2, R36.2, TP6.1, U1.3 (GND), U1.8 (GND), U2.3 (GND), U2.8 (GND), U3.19 (SHIELD), U3.20 (SHIELD), U4.3 (GND), U4.8 (GND), U5.3 (GND), U6.37 (VSS), U7.2 (GND), U8.4 (VSS), U9.3 (GND), U11.4 (GND), U12.3 (GND), U13.5 (GND), U13.10 (nOE), U14.3 (GND), U15.7 (GND), U15.9 (EP), U16.7 (GND), U16.9 (EP), U18.2 (GND)
unnamed: BT1.1 (+), D3.1
unnamed: C1.1, U3.4 (CT), U3.5 (CT)
unnamed: C8.1, U6.33 (XTALIN/CLKIN), Y1.1
unnamed: C9.1, U6.32 (XTALOUT), Y1.2
unnamed: C24.1, R20.1, U14.2
unnamed: C29.1, R22.2
unnamed: C29.2, U15.1 (BST)
unnamed: C36.1, J19.1, Q1.5 (D)
unnamed: C40.2, D4.2 (A), Q1.4 (G), R26.1
unnamed: C46.1, D3.3, U8.8 (VDD)
unnamed: C57.1, R9.2
unnamed: C57.2, U16.1 (BST)
unnamed: C58.1, U16.4 (SS)
unnamed: C59.1, R25.1, U16.6 (COMP)
unnamed: C60.1, R25.2
unnamed: C61.2, R27.2, R28.1, U16.5 (FB)
unnamed: C62.1, U15.4 (SS)
unnamed: C63.1, R23.1, U15.6 (COMP)
unnamed: C64.1, R23.2
unnamed: C65.2, R24.2, R30.1, U15.5 (FB)
unnamed: D1.1 (K), R10.1, TP5.1
unnamed: D2.1 (K), R1.1, TP3.1
unnamed: J2.13, U9.4
unnamed: J7.9 (DET_B), R18.2
unnamed: J7.10 (DET_A), R17.2
unnamed: J11.1 (VBUS), R8.1
unnamed: J17.3, R21.1, U11.6 (TACH)
unnamed: J17.4, U11.5 (PWM)
unnamed: L3.1, R22.1, U15.8 (SW)
unnamed: L5.1, R9.1, U16.8 (SW)
unnamed: Module1.21 (PI_nLED_Activity), R1.2
unnamed: R2.1, U3.16 (LEDG_K)
unnamed: R3.1, U3.18 (LEDY_K)
unnamed: R10.2, U5.4
unnamed: R12.1, U6.24 (SCL/SMBCLK/CFG_SEL0)
unnamed: R13.1, U6.22 (SDA/SMBDATA/NON_REM1)
unnamed: R14.1, U6.28 (SUSP_IND/LOCAL_PWR/NON_REM0)
unnamed: R15.2, U6.35 (RBIAS)
unnamed: R16.1, U6.25 (HS_IND/CFG_SEL1)
unnamed: R36.1, U7.5 (ILIM)
unnamed: U4.1 (D1+), U4.10
unnamed: U4.2 (D1-), U4.9
unnamed: U8.1 (OSCI), Y2.2
unnamed: U8.2 (OSCO), Y2.1

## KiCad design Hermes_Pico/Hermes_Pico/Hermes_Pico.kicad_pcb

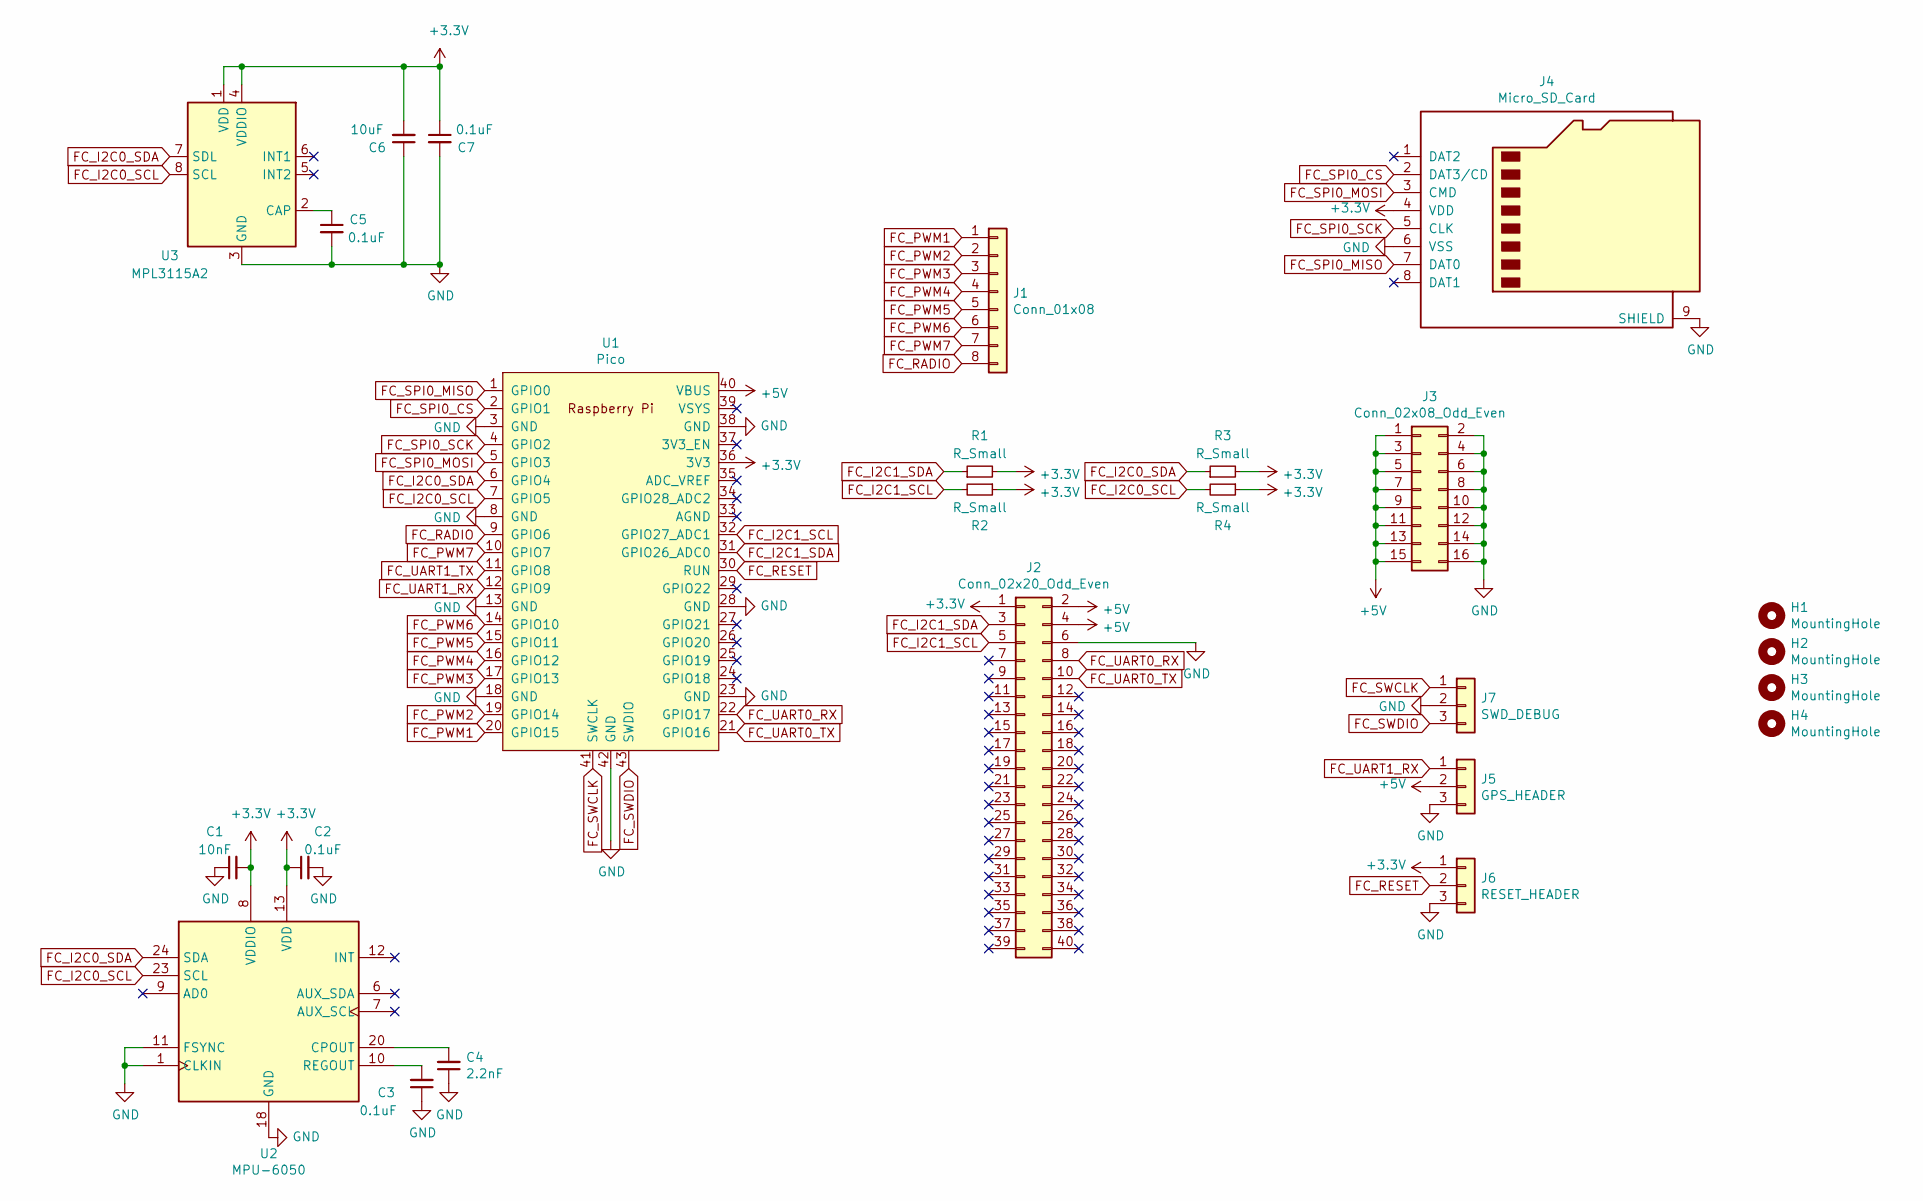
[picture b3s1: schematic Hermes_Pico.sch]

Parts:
C1: 10nF; C_0402_1005Metric; LCSC C15195
C2, C3, C5, C7: 0.1uF; C_0402_1005Metric; LCSC C307331
C4: 2.2nF; C_0402_1005Metric; LCSC C1531
C6: 10uF; C_0402_1005Metric; LCSC C15525
H1, H2, H3, H4: MountingHole; MountingHole_2.5mm
J1: Conn_01x08; PinHeader_1x08_P2.54mm_Vertical
J2: Conn_02x20_Odd_Even; PinHeader_2x20_P2.54mm_Vertical
J3: Conn_02x08_Odd_Even; PinHeader_2x08_P2.54mm_Vertical
J4: Micro_SD_Card; microSD_HC_Wuerth_693072010801; LCSC C164170
J5: GPS_HEADER; PinHeader_1x03_P2.54mm_Vertical
J6: RESET_HEADER; PinHeader_1x03_P2.54mm_Vertical
J7: SWD_DEBUG; PinHeader_1x03_P2.54mm_Vertical
R1, R2, R3, R4: R_Small; R_0402_1005Metric; LCSC C25900
U1: Pico; RPi_Pico_SMD_TH
U2: MPU-6050; InvenSense_QFN-24_4x4mm_P0.5mm; LCSC C24112
U3: MPL3115A2; NXP_LGA-8_3x5mm_P1.25mm_H1.1mm

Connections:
+3V3: C1.2, C2.1, C6.2, C7.1, J2.1, J4.4 (VDD), J6.1, R1.2, R2.1, R3.2, R4.1, U1.36 (3V3), U2.8 (VDDIO), U2.13 (VDD), U3.1 (VDD), U3.4 (VDDIO)
+5V: J2.2, J2.4, J3.1, J3.3, J3.5, J3.7, J3.9, J3.11, J3.13, J3.15, J5.2, U1.40 (VBUS)
FC_I2C0_SCL: R4.2, U1.7 (GPIO5), U2.23 (SCL), U3.8 (SCL)
FC_I2C0_SDA: R3.1, U1.6 (GPIO4), U2.24 (SDA), U3.7 (SDL)
FC_I2C1_SCL: J2.5, R2.2, U1.32 (GPIO27_ADC1)
FC_I2C1_SDA: J2.3, R1.1, U1.31 (GPIO26_ADC0)
FC_PWM1: J1.1, U1.20 (GPIO15)
FC_PWM2: J1.2, U1.19 (GPIO14)
FC_PWM3: J1.3, U1.17 (GPIO13)
FC_PWM4: J1.4, U1.16 (GPIO12)
FC_PWM5: J1.5, U1.15 (GPIO11)
FC_PWM6: J1.6, U1.14 (GPIO10)
FC_PWM7: J1.7, U1.10 (GPIO7)
FC_RADIO: J1.8, U1.9 (GPIO6)
FC_RESET: J6.2, U1.30 (RUN)
FC_SPI0_CS: J4.2 (DAT3/CD), U1.2 (GPIO1)
FC_SPI0_MISO: J4.7 (DAT0), U1.1 (GPIO0)
FC_SPI0_MOSI: J4.3 (CMD), U1.5 (GPIO3)
FC_SPI0_SCK: J4.5 (CLK), U1.4 (GPIO2)
FC_SWCLK: J7.1, U1.41 (SWCLK)
FC_SWDIO: J7.3, U1.43 (SWDIO)
FC_UART0_RX: J2.8, U1.22 (GPIO17)
FC_UART0_TX: J2.10, U1.21 (GPIO16)
FC_UART1_RX: J5.1, U1.12 (GPIO9)
FC_UART1_TX: U1.11 (GPIO8)
GND: C1.1, C2.2, C3.1, C4.1, C5.2, C6.1, C7.2, J2.6, J3.2, J3.4, J3.6, J3.8, J3.10, J3.12, J3.14, J3.16, J4.6 (VSS), J4.9 (SHIELD), J5.3, J6.3, J7.2, U1.3 (GND), U1.8 (GND), U1.13 (GND), U1.18 (GND), U1.23 (GND), U1.28 (GND), U1.38 (GND), U1.42 (GND), U2.1 (CLKIN), U2.11 (FSYNC), U2.18 (GND), U3.3 (GND)
unnamed: C3.2, U2.10 (REGOUT)
unnamed: C4.2, U2.20 (CPOUT)
unnamed: C5.1, U3.2 (CAP)

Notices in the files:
parts and their libraries:
Copyright 2021 Accelerated Designs. All rights reserved.
